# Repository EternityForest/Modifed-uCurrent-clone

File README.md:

Modifed-uCurrent-clone
======================

A clone of the ucurrent by dave jones using more common  parts

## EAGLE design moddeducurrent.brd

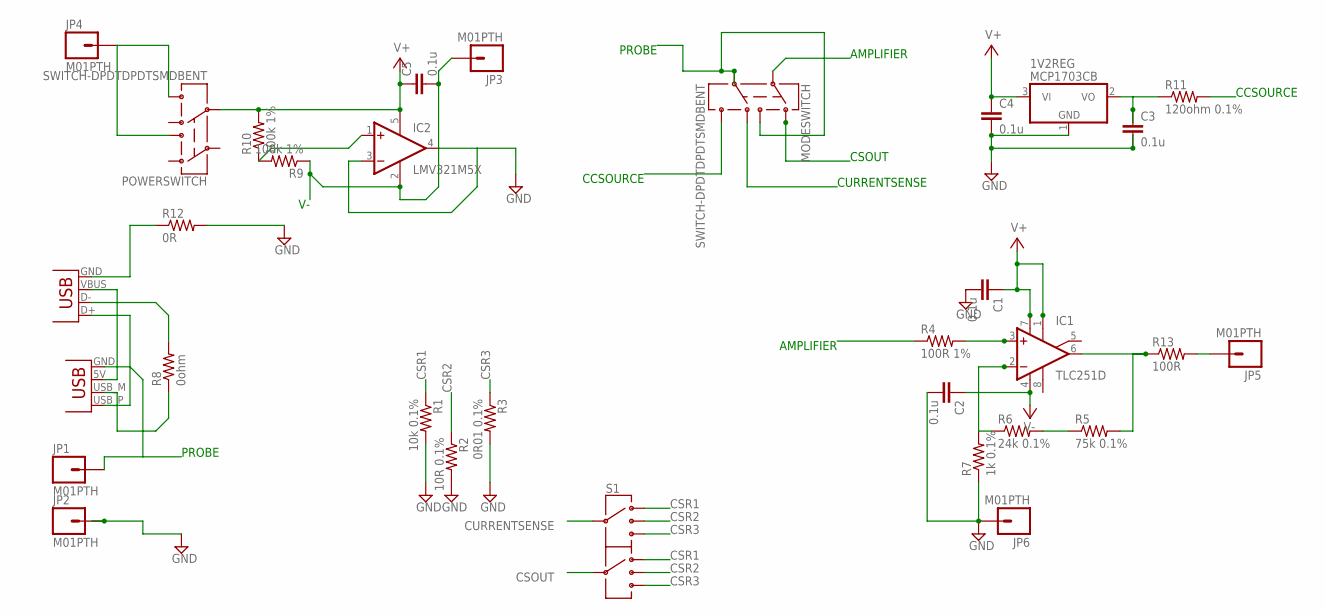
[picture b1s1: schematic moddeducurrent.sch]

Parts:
1V2REG: MCP1703CB; SOT23
C1, C2, C3, C4, C5: 0.1u; 0805
IC1: TLC251D; SO08
IC2: LMV321M5X; SOT23-5
JP1, JP2, JP3, JP4, JP5, JP6: M01PTH; 1X01
MODESWITCH: SWITCH-DPDTDPDTSMDBENT; AYZ0202
POWERSWITCH: SWITCH-DPDTDPDTSMDBENT; AYZ0202
R1: 10k 0.1%; 0805
R2: 10R 0.1%; 0805
R3: 0R01 0.1%; 0805
R4: 100R 1%; 0805
R5: 75k 0.1%; 0805
R6: 24k 0.1%; 0805
R7: 1k 0.1%; 0805
R8: 0ohm; 0805
R9, R10: 100k 1%; 0805
R11: 120ohm 0.1%; 0805
R12: 0R; 0805
R13: 100R; 0805
S1: SWITCH-DP3T; SWITCH-DP3T-SMD
X1: USBPCB; USB-A-PCB
X2: USBOLD; USB-MINIB-OLD

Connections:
AMPIN: MODESWITCH.2, R4.1
CCSOURCE: MODESWITCH.6, R11.2
CSOUT: MODESWITCH.1, S1.BI
CSR1: R1.1, S1.A1, S1.B1
CSR2: R2.1, S1.A2, S1.B2
CSR3: R3.1, S1.A3, S1.B3
CURRENTSENSE: MODESWITCH.4, S1.AI
GND: 1V2REG.1 (GND), C1.2, C2.2, C3.2, C4.2, IC2.3 (-IN), IC2.4 (OUT), JP2.1, JP6.1, R1.2, R2.2, R3.2, R7.1, R12.2
unnamed: JP5.1, R13.2
unnamed: 1V2REG.2 (VO), C3.1, R11.1
unnamed: R12.1, X2.GND
unnamed: IC1.3 (+IN), R4.2
unnamed: R5.1, R6.2
unnamed: IC1.2 (-IN), R6.1, R7.2
unnamed: R8.2, X2.D-
unnamed: X1.USB_P (D+), X2.D+
unnamed: R8.1, X1.USB_M (D-)
unnamed: IC2.1 (+IN), R9.2, R10.1
OUT: IC1.6 (OUT), R5.2, R13.1
PROBE: JP1.1, MODESWITCH.3, MODESWITCH.5, X1.GND
V+: 1V2REG.3 (VI), C1.1, C4.1, C5.1, IC1.1 (ON1), IC1.7 (V+), IC2.5 (V+), POWERSWITCH.5, R10.2
V-: C2.1, C5.2, IC1.4 (V-), IC2.2 (V-), JP3.1, R9.1
VBAT: JP4.1, POWERSWITCH.3, POWERSWITCH.6
VUSB_EXTERN: X1.5V (VBUS), X2.VBUS

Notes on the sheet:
PROBE
AMPLIFIER
CURRENTSENSE
CSOUT
CCSOURCE

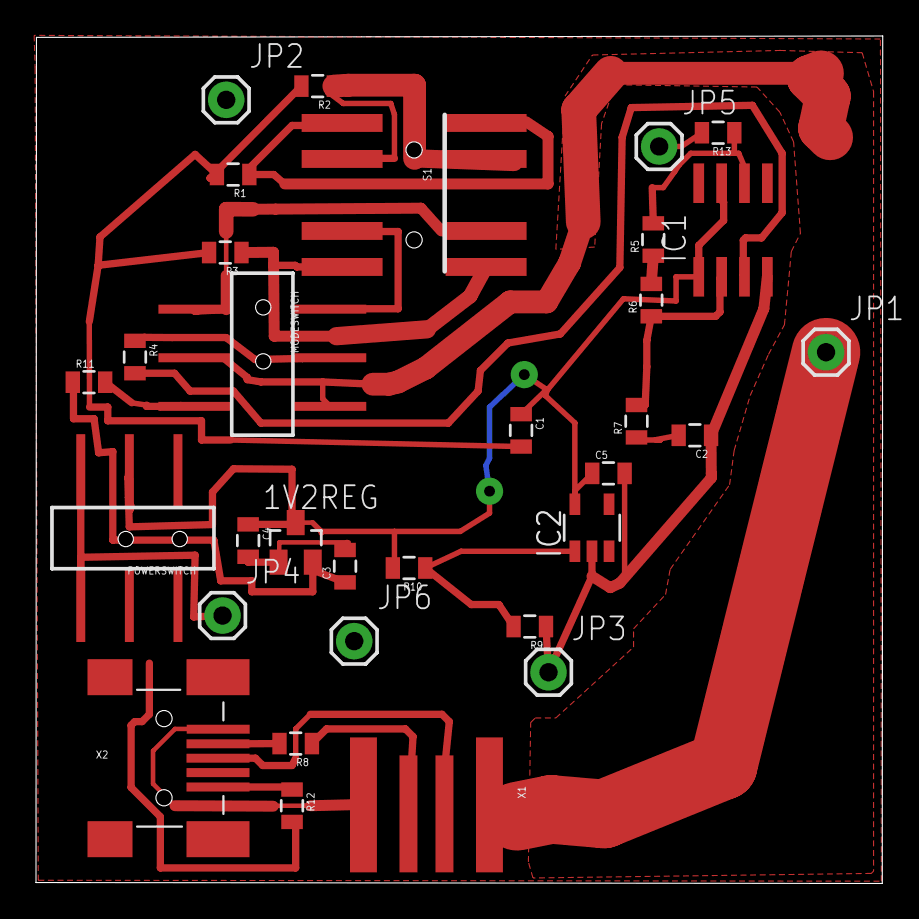
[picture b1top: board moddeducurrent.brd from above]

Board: 2 copper layers, 47.0 x 47.1 mm, 32 parts (0 on the bottom side), 24 nets.

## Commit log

2012-05-30 Initial commit. Changed the 3 position switch to two 2 position switches.
2012-05-31 Added most of the power supply section. Still needs component values, IO connections, and somebody needs to look over my USB data lines. Also needs battery holder.
2012-08-15 EXPERIMENTAL---UNTESTED--NEEDS DOUBLE CHECKING Needs parts values. Added pads for external connectors Added milliohm-meter option Added external battery option
2012-08-17 Separated into parts for readability. NOTE USB device current measuring won't work unless your usb device needs 20ma of 2.5v.
2012-08-27 Simplified design. Had to ditch the USB power option or else ad a charge pump. 2 fewer components. No usb power but USB measurement availible. The current path runs through a few switches so there co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
    The Milliohm Meter mode uses a current source of ~10ma for very low resistances.
    The Vreg is a 0.4% accuracy source and the resistor under test should be under 1.2ohms to stay within a few percent accuracy.
    The probes will double as a 0.4% 1.2v voltage standard for quick t
2012-09-14 Updated main switch to dp3t
2012-09-24 current traces no longer shared with voltage traces.
2012-09-24 Added missing input capacitor on 1V2REG just in case, fixed a piee of atrocious routing on the output cap of the same, beefed up the main current carrying trace.
2012-10-24 Changed switch to cheaper ebay switch. Added signal plane.
2013-04-20 added resistor values
